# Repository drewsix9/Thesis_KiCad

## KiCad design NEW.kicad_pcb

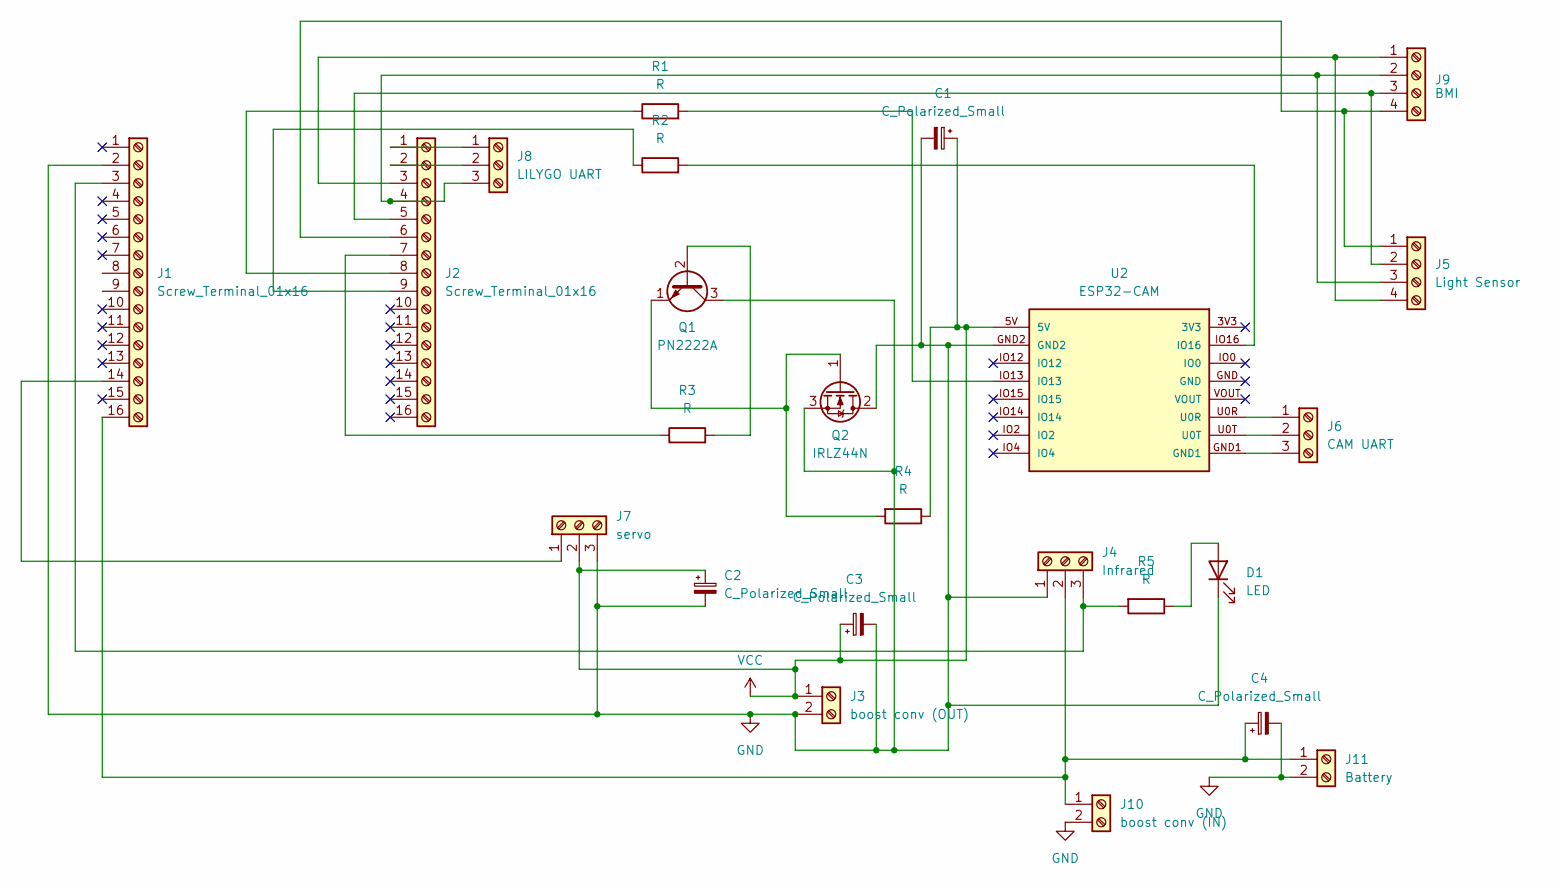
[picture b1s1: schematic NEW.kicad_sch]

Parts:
C1, C2, C3, C4: C_Polarized_Small; C_Disc_D3.8mm_W2.6mm_P2.50mm
D1: LED; LED_D5.0mm
J1, J2: Screw_Terminal_01x16; PinHeader_1x16_P2.54mm_Vertical
J3: boost conv (OUT); TerminalBlock_Altech_AK300-2_P5.00mm
J4: Infrared; PinHeader_1x03_P2.54mm_Vertical
J5: Light Sensor; PinHeader_1x04_P2.54mm_Vertical
J6: CAM UART; PinHeader_1x03_P2.54mm_Vertical
J7: servo; PinHeader_1x03_P2.54mm_Vertical
J8: LILYGO UART; PinHeader_1x03_P2.54mm_Vertical
J9: BMI; PinHeader_1x04_P2.54mm_Vertical
J10: boost conv (IN); TerminalBlock_Altech_AK300-2_P5.00mm
J11: Battery; TerminalBlock_Altech_AK300-2_P5.00mm
Q1: PN2222A; TO-92_Inline_Wide
Q2: IRLZ44N; TO-220-3_Vertical
R1, R2, R3, R4, R5: R; R_Axial_DIN0207_L6.3mm_D2.5mm_P7.62mm_Horizontal
U2: ESP32-CAM

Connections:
GND: C1.2, C2.2, C3.2, C4.2, D1.1 (K), J1.2, J3.2, J4.1, J7.3, J10.2, J11.2, Q1.3 (C), Q2.2 (D), Q2.3 (S), U2.GND2
unnamed: D1.2 (A), R5.1
unnamed: J1.3, J4.3, R5.2
unnamed: J1.14, J7.1
unnamed: C4.1, J1.16, J4.2, J10.1, J11.1
unnamed: J2.1, J8.1
unnamed: J2.2, J8.2
unnamed: J2.3, J5.4, J9.1
unnamed: J2.4, J5.3, J8.3, J9.2
unnamed: J2.5, J5.2, J9.3
unnamed: J2.6, J5.1, J9.4
unnamed: J2.7, R3.1
unnamed: J2.8, R1.1
unnamed: J2.9, R2.1
unnamed: J6.1, U2.U0R
unnamed: J6.2, U2.U0T
unnamed: J6.3, U2.GND1
unnamed: Q1.2 (B), R3.2
unnamed: Q1.1 (E), Q2.1 (G), R4.2
unnamed: R1.2, U2.IO13
unnamed: R2.2, U2.IO16
VCC: C1.1, C2.1, C3.1, J3.1, J7.2, R4.1, U2.5V

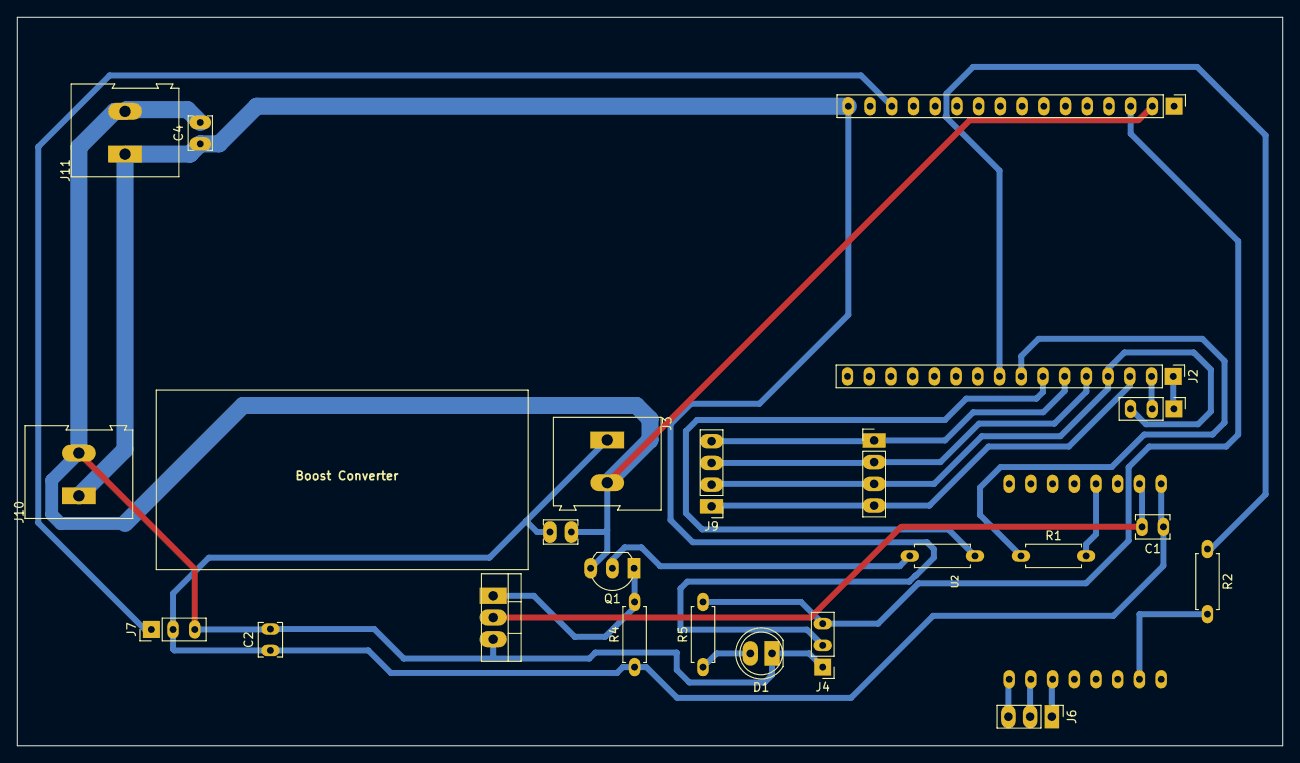
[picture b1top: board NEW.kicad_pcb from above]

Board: 2 copper layers, 148.0 x 85.2 mm, 24 parts (0 on the bottom side), 22 nets.

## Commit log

2026-04-17 fixed proper wiring on power
2026-04-18 final rev
